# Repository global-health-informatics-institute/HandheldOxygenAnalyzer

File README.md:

# HandheldOxygenAnalyzer
All necessary files about the prototype

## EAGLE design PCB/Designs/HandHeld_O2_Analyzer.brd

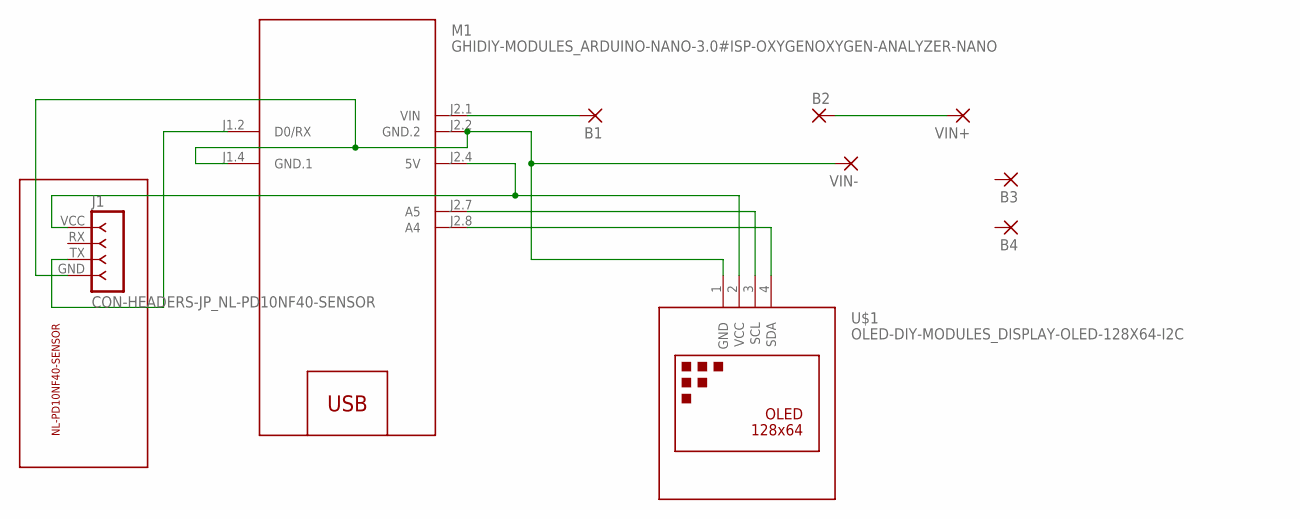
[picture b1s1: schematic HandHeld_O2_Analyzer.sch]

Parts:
B1, B2, B3, B4: 2,54/0,8
J1: CON-HEADERS-JP_NL-PD10NF40-SENSOR
M1: GHIDIY-MODULES_ARDUINO-NANO-3.0#ISP-OXYGENOXYGEN-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; GHIDIY-MODULES_ARDUINO-NANO-3.0#ISP-OXYGEN
U$1: OLED-DIY-MODULES_DISPLAY-OLED-128X64-I2C
VIN+: WIREPAD_2,54/0,8
VIN-: WIREPAD_2,54/0,8

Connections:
unnamed: M1.J2.8 (A4), U$1.4 (SDA)
unnamed: M1.J2.7 (A5), U$1.3 (SCL)
unnamed: J1.GND, M1.J1.4 (GND.1), M1.J2.2 (GND.2), U$1.1 (GND), VIN-.1
unnamed: J1.VCC, M1.J2.4 (5V), U$1.2 (VCC)
unnamed: B1.1, M1.J2.1 (VIN)
unnamed: B2.1, VIN+.1
unnamed: J1.TX, M1.J1.2 (D0/RX)

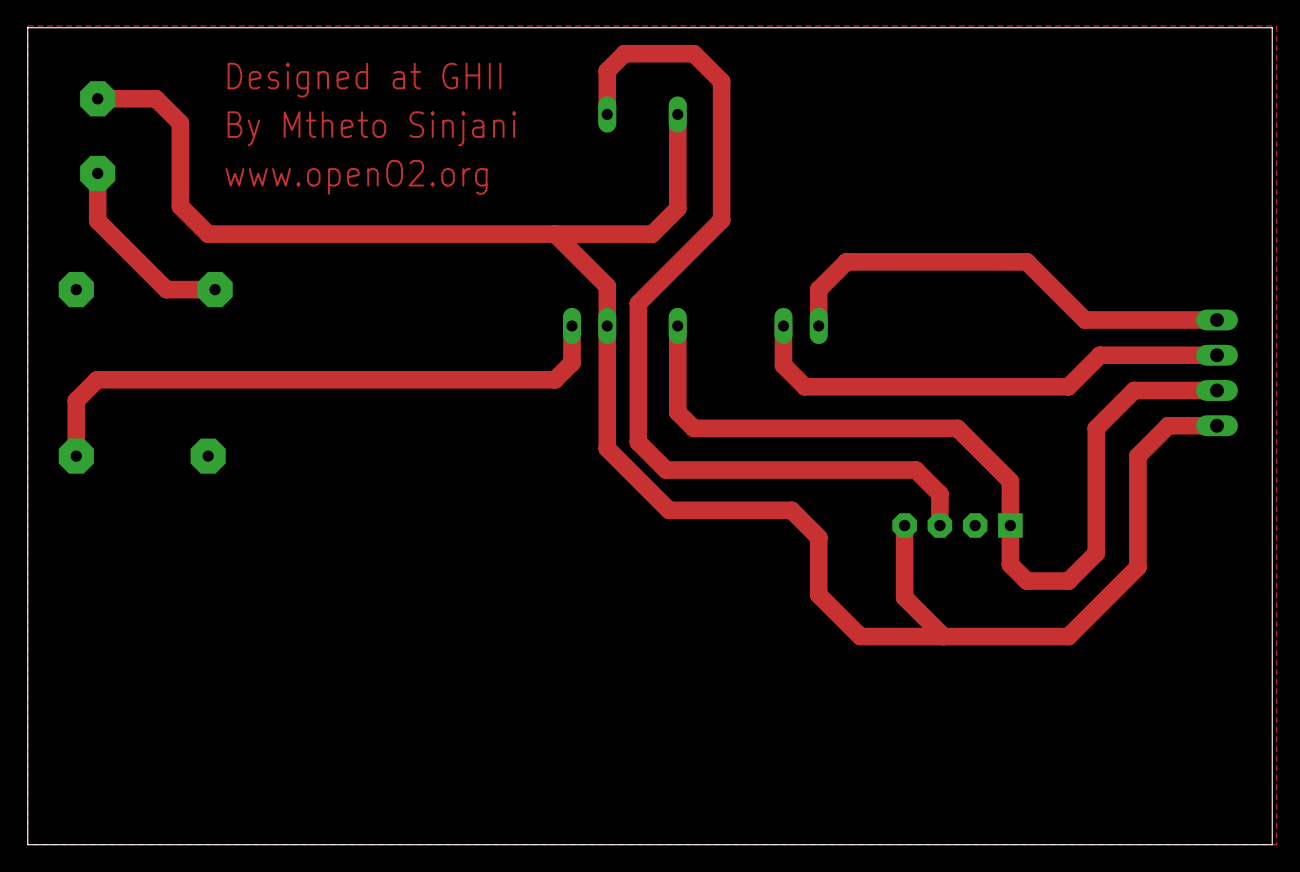
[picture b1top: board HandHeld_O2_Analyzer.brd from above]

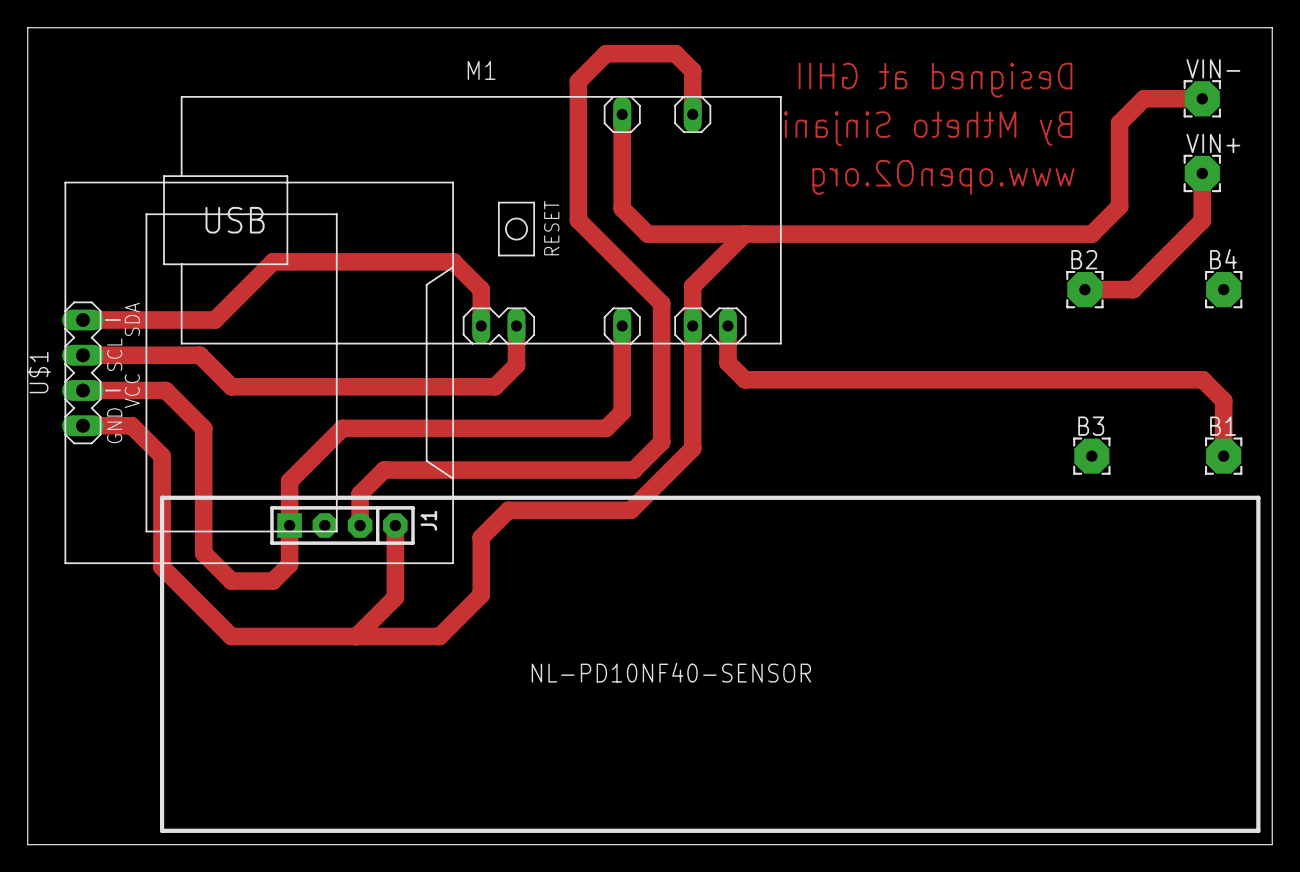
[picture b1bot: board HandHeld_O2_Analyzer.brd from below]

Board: 2 copper layers, 89.7 x 58.9 mm, 9 parts (9 on the bottom side), 7 nets.

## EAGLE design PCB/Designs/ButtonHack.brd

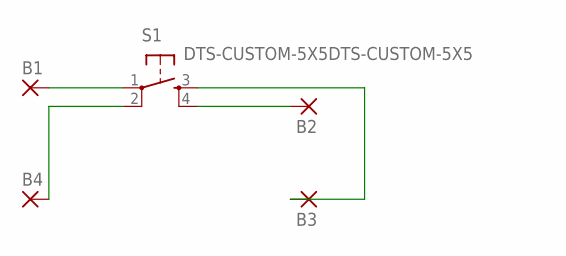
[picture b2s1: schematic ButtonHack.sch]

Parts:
B1, B2, B3, B4: 2,54/0,8
S1: DTS-CUSTOM-5X5DTS-CUSTOM-5X5; DTS-CUSTOM-5X5

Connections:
unnamed: B1.1, S1.1
unnamed: B2.1, S1.4
unnamed: B4.1, S1.2
unnamed: B3.1, S1.3

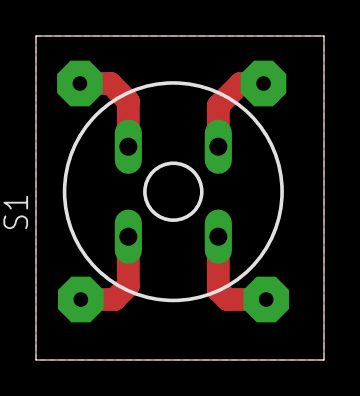
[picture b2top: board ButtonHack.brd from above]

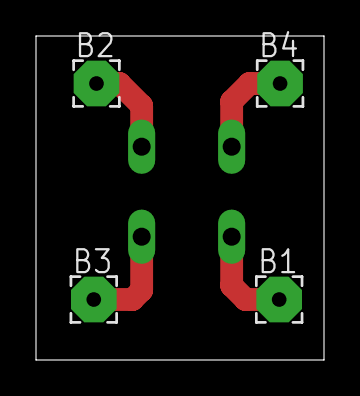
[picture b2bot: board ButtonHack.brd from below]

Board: 2 copper layers, 16.0 x 18.0 mm, 5 parts (4 on the bottom side), 4 nets.

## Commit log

2022-01-21 For the power button
2022-01-21 Resources
2022-03-21 3D Designs
2022-05-10 C++ code for oxygen analyzer
2024-02-02 Add files via upload
    Hand held analyser code that includes the pressure sensor
